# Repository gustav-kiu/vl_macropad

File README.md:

This is my first hardware project I've ever did! I've made a lot of mistakes making it this far; I lost the count on  how many times I redesigned both the PCB and the case being sure it would be the last time.

On the PCB I'd maybe just put the mcu on the other side (again). Other than that, there doesn't seems to be much else to be improve on the PCB, though some silly art on the silkscreen could be added.

# vl_macropad

vl_macropad is an 8 key macropad with a rotary encoder, using QMK firmware. The mcu used is the Xiao RP2040

# Features

 - 8 mechanical MX-style switches(soldered)
 - An EC11 rotary encoder
 - 8 SK6812MINI-E LEDs for backlight(I hope)

# CAD Model

The structure of this macropad is heavily inspired* by the sandwich-style structure of mechanical keyboards. 

There are no heatset inserts used in this design to keep the profile a little bit smaller(though it could be smaller imo). It's (supposed to be) held together by 4 16mm M3 screws that are exactly about 16mm long because otherwise the top part will break or not be held down properly.

> Some 3d renders I got a bit carried away making
> 
>

# PCB

The PCB which is a 2-layer one I made in kicad. This is the result after a couple of iterations.

> Schematic
>
> 

> PCB
>
> 
> 
> 

The pcb is 99.06mm x 41.91mm in size.

# Firmware

The firmware in use is QMK.

At the moment I have no idea whether the firmware works at all

# Layout

## Base layer(BL)

the *default* behaviour

Encoder CW/CCW - volume up/down; press - mute

|  |  |  |  |  |
|---|---|---|---|---|
| F13 | F14 | media  previous | media next |  |
| F15 | F16 | F17 | media play/pause | audio mute/unmute |

# BOM

| Item | Qty |
|---|---|
| 1N4148 diode | 8 |
| SK6812MINI-E LED | 8 |
| MX-style switch | 8 |
| DSA keycap | 8 |
| EC11 Rotary encoder | 1 |
| XIAO RP2040 | 1 |
| M3x16mm screw | 4 |
| Case (3 printed parts) | 1 |
| PCB | 1 |

# Does it work??

I did try to make it according to the design. The first trouble was the LEDs. The LED's on the firt board I assembled just seemed to have shorted out and drew just about as much current as could. I couldn't get as much as a single led working. Therefore I ommited the LEDs from the next boards I assembled. After making modifications to the firmware, **it did work**, however after a couple of days it started booting into the bootloader mode. Given it worked before, it's probably just a skill issue of mine.

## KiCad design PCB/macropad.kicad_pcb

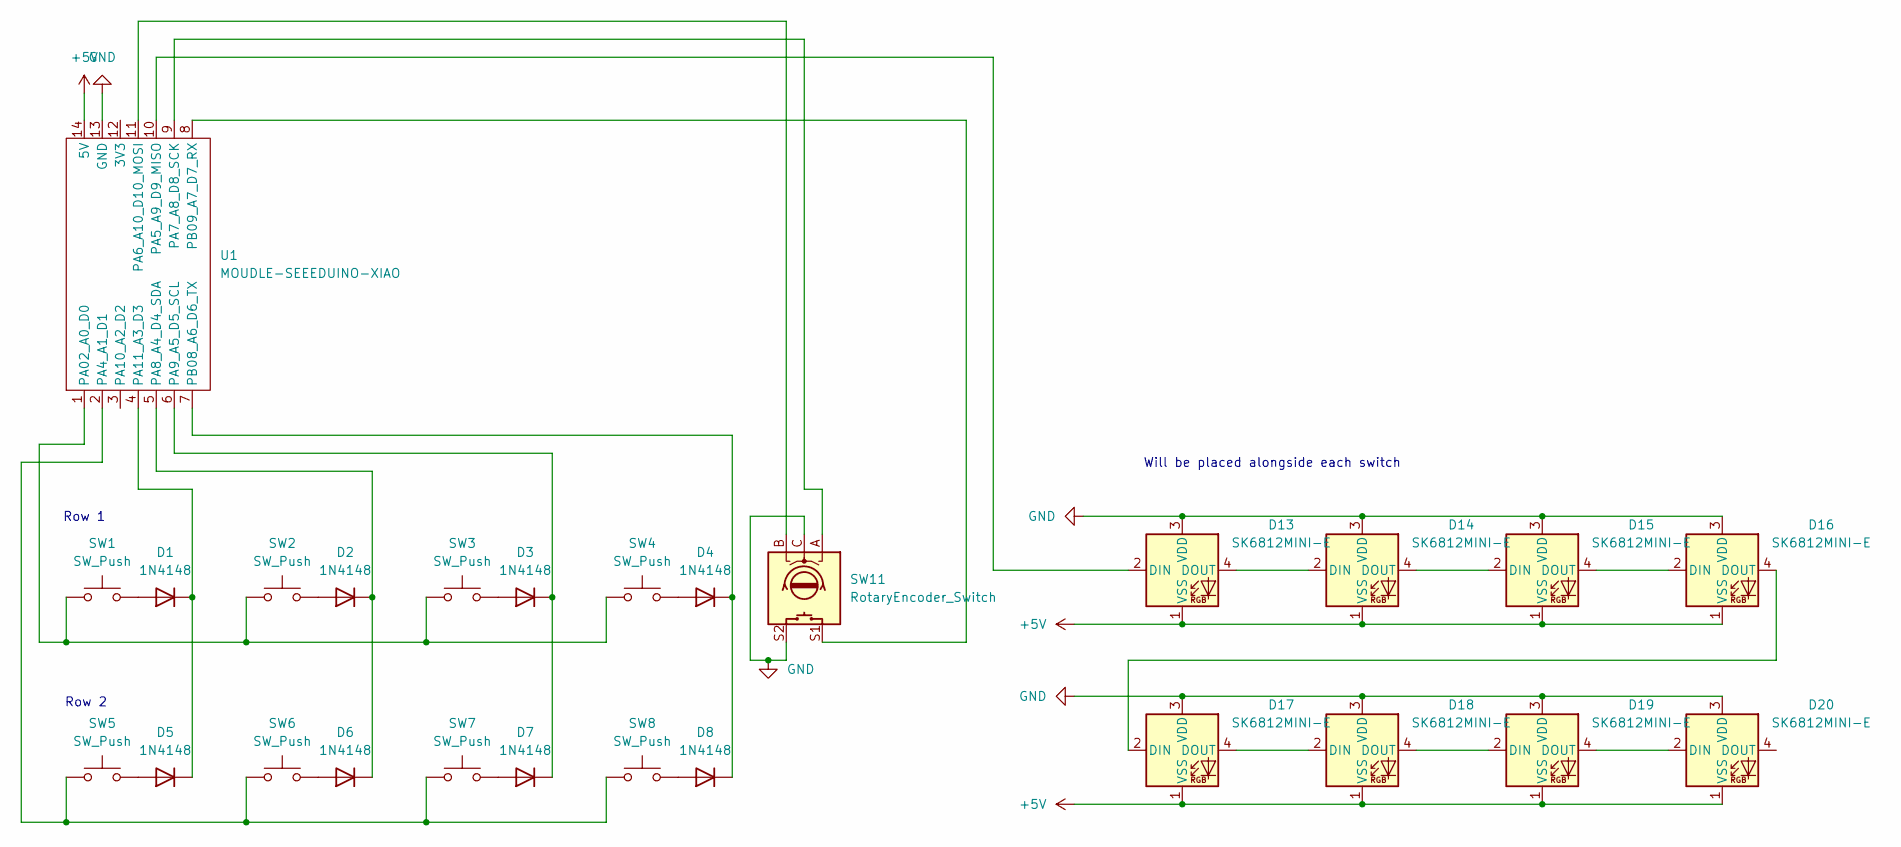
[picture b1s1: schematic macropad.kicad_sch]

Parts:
D1, D2, D3, D4, D5, D6, D7, D8: 1N4148; D_DO-35_SOD27_P7.62mm_Horizontal
D13, D14, D15, D16, D17, D18, D19, D20: SK6812MINI-E; LED_SK6812MINI-E_3.2x2.8mm_P1.5mm_ReverseMount
SW1, SW2, SW3, SW4, SW5, SW6, SW7, SW8: SW_Push; SW_Cherry_MX_1.00u_PCB
SW11: RotaryEncoder_Switch; RotaryEncoder_Alps_EC11E-Switch_Vertical
U1: MOUDLE-SEEEDUINO-XIAO; XIAO-Generic-Hybrid-14P-2.54-21X17.8MM

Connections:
+5V: D13.1 (VSS), D14.1 (VSS), D15.1 (VSS), D16.1 (VSS), D17.1 (VSS), D18.1 (VSS), D19.1 (VSS), D20.1 (VSS), U1.14 (5V)
GND: D13.3 (VDD), D14.3 (VDD), D15.3 (VDD), D16.3 (VDD), D17.3 (VDD), D18.3 (VDD), D19.3 (VDD), D20.3 (VDD), SW11.C, SW11.S2, U1.13 (GND)
unnamed: D1.2 (A), SW1.2
unnamed: D1.1 (K), D5.1 (K), U1.4 (PA11_A3_D3)
unnamed: D2.2 (A), SW2.2
unnamed: D2.1 (K), D6.1 (K), U1.5 (PA8_A4_D4_SDA)
unnamed: D3.2 (A), SW3.2
unnamed: D3.1 (K), D7.1 (K), U1.6 (PA9_A5_D5_SCL)
unnamed: D4.2 (A), SW4.2
unnamed: D4.1 (K), D8.1 (K), U1.7 (PB08_A6_D6_TX)
unnamed: D5.2 (A), SW5.2
unnamed: D6.2 (A), SW6.2
unnamed: D7.2 (A), SW7.2
unnamed: D8.2 (A), SW8.2
unnamed: D13.2 (DIN), U1.10 (PA5_A9_D9_MISO)
unnamed: D13.4 (DOUT), D14.2 (DIN)
unnamed: D14.4 (DOUT), D15.2 (DIN)
unnamed: D15.4 (DOUT), D16.2 (DIN)
unnamed: D16.4 (DOUT), D17.2 (DIN)
unnamed: D17.4 (DOUT), D18.2 (DIN)
unnamed: D18.4 (DOUT), D19.2 (DIN)
unnamed: D19.4 (DOUT), D20.2 (DIN)
unnamed: SW1.1, SW2.1, SW3.1, SW4.1, U1.1 (PA02_A0_D0)
unnamed: SW5.1, SW6.1, SW7.1, SW8.1, U1.2 (PA4_A1_D1)
unnamed: SW11.B, U1.11 (PA6_A10_D10_MOSI)
unnamed: SW11.A, U1.9 (PA7_A8_D8_SCK)
unnamed: SW11.S1, U1.8 (PB09_A7_D7_RX)

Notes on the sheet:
Row 2
Will be placed alongside each switch
Row 1

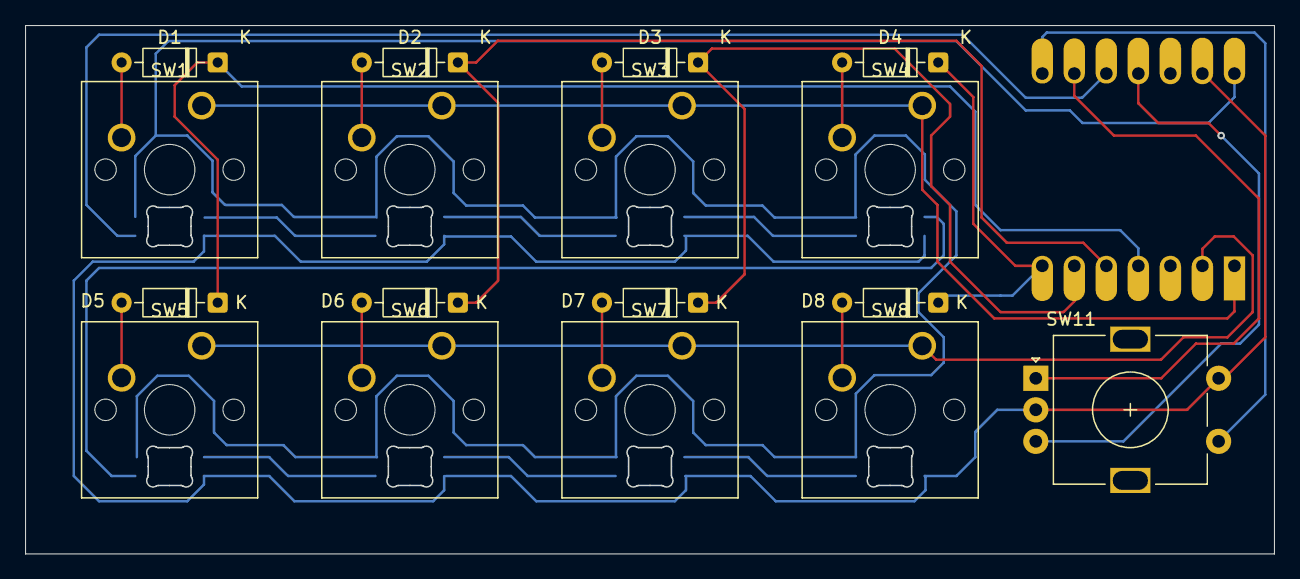
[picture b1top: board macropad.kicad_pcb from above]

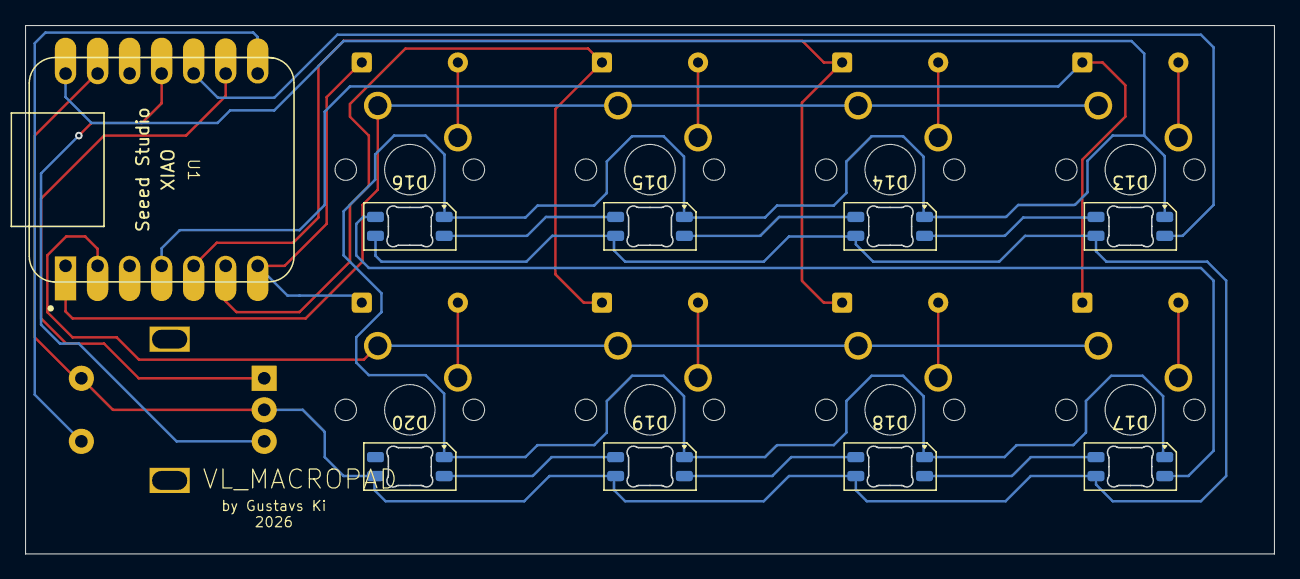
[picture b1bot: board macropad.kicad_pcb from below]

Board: 2 copper layers, 99.1 x 41.9 mm, 26 parts (9 on the bottom side), 27 nets.
